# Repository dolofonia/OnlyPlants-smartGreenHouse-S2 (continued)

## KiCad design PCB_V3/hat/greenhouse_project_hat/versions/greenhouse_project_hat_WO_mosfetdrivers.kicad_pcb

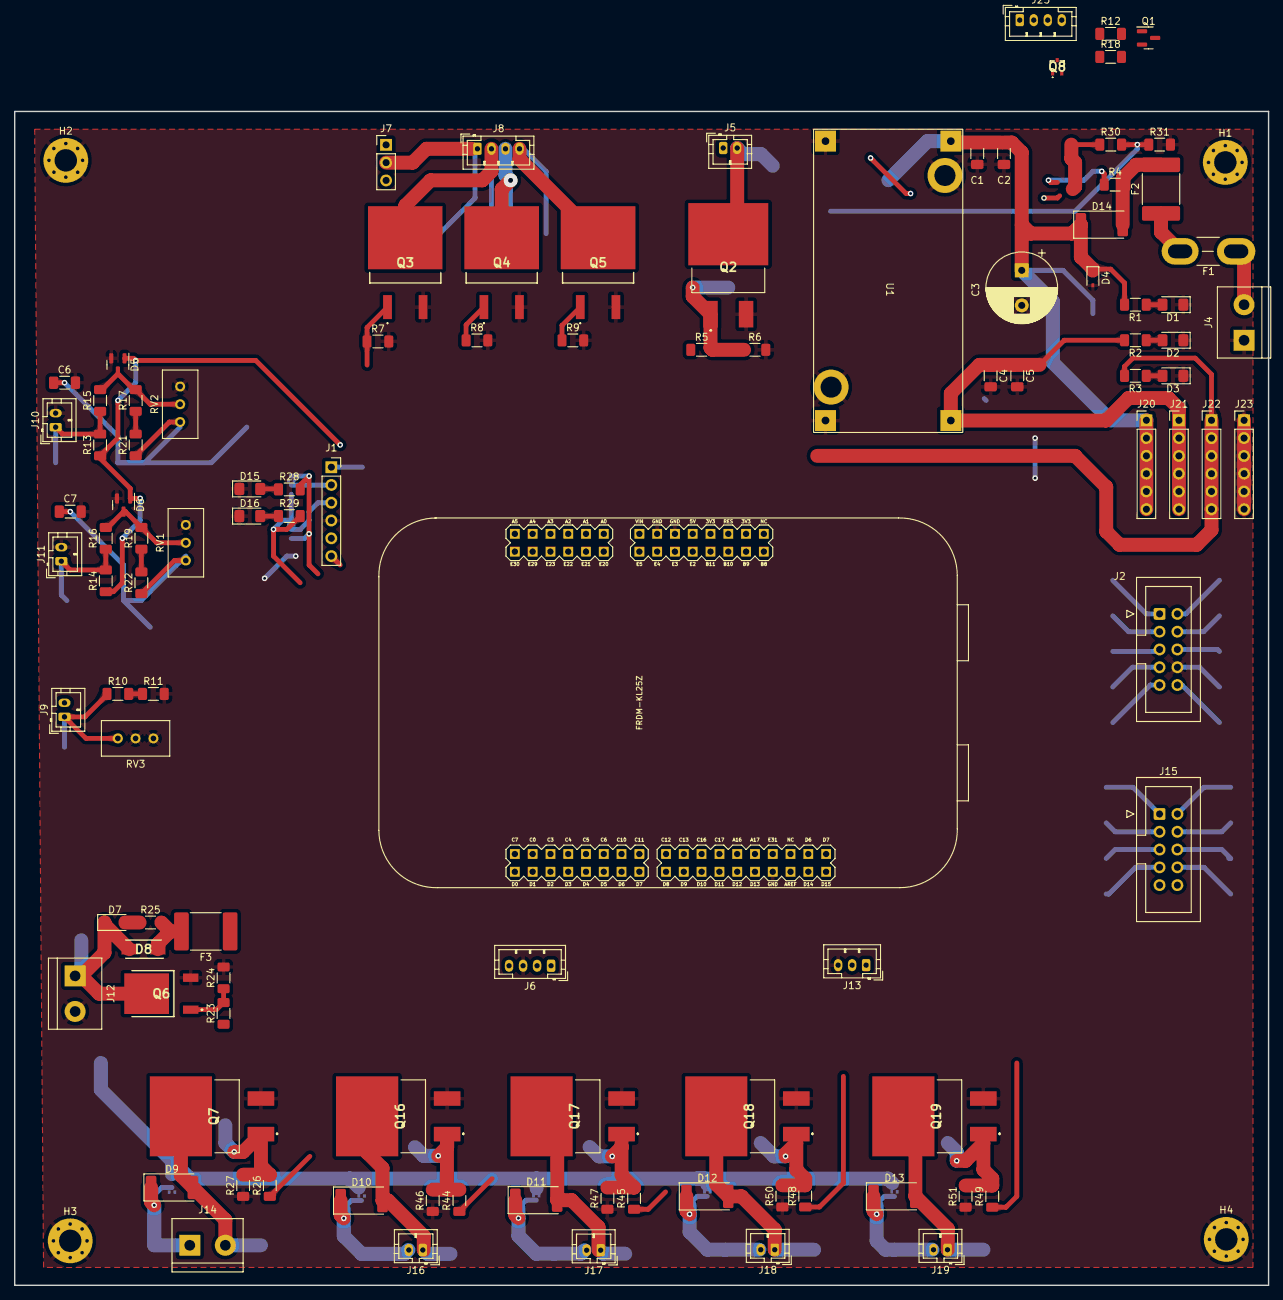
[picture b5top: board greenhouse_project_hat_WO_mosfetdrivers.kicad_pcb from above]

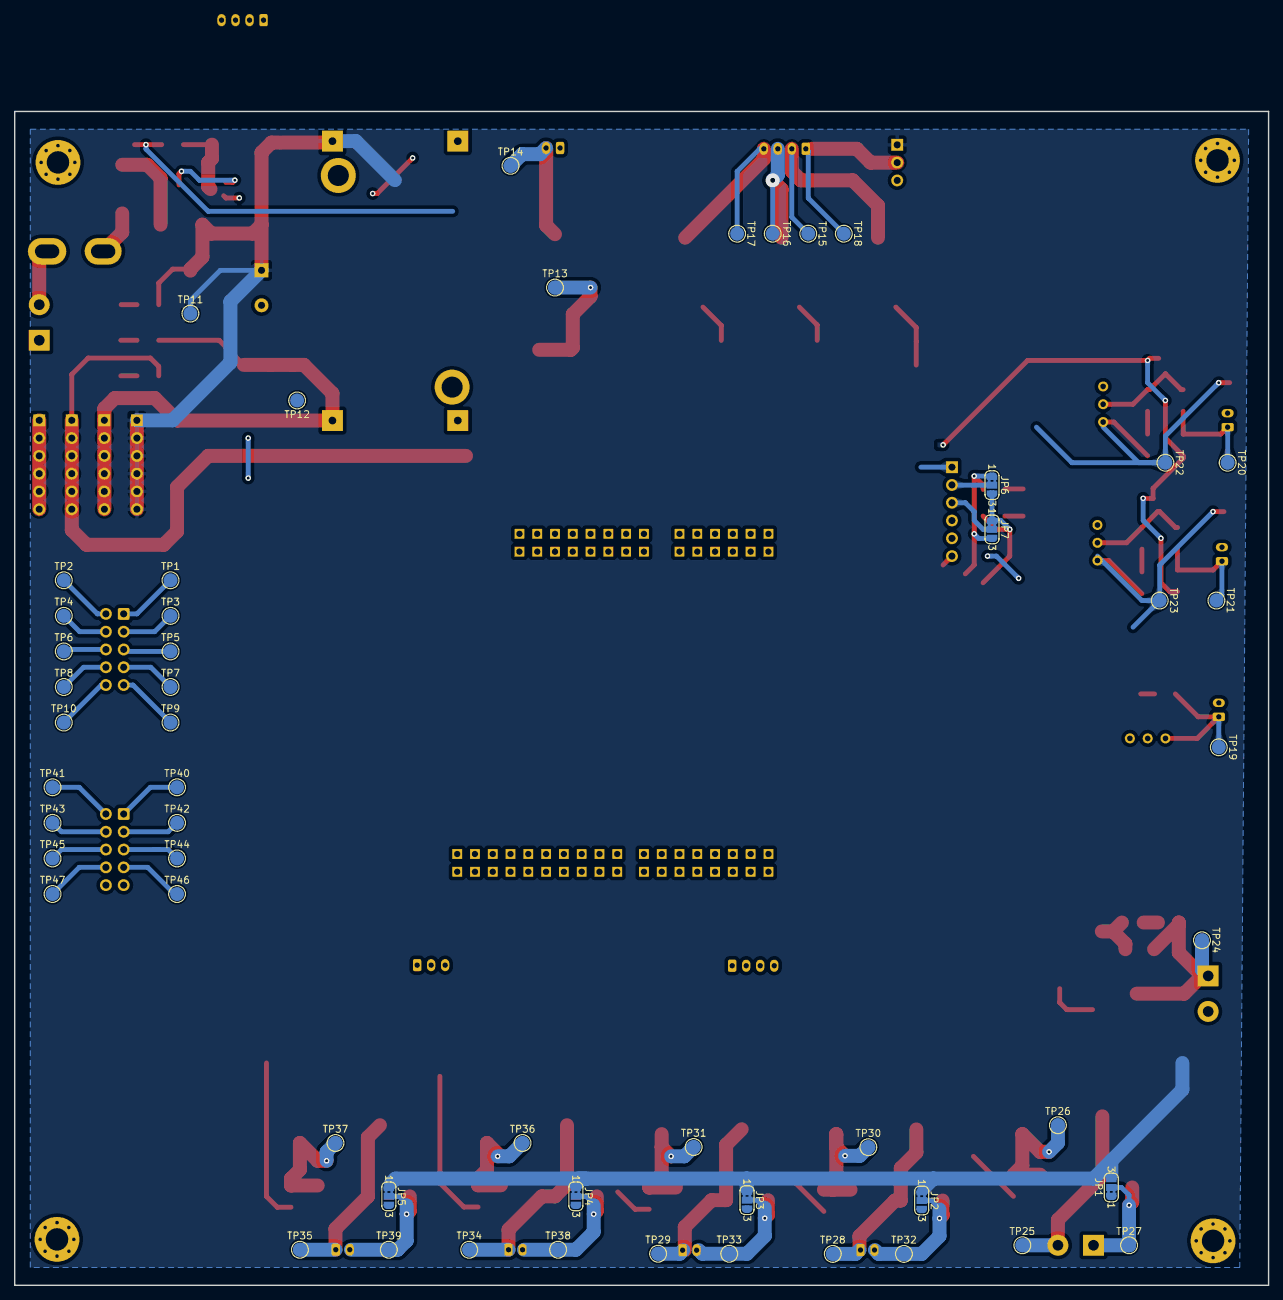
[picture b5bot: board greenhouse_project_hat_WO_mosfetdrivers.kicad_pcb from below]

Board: 4 copper layers, 179.1 x 167.6 mm, 166 parts (57 on the bottom side), 87 nets.

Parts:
C1, C5, C6, C7: 0.1uF; C_1206_3216Metric_Pad1.33x1.80mm_HandSolder
C2, C4: 10uF; C_1206_3216Metric_Pad1.33x1.80mm_HandSolder
C3: 1000uF; CP_Radial_D10.0mm_P5.00mm
D1, D2, D3, D7, D15, D16: LED; LED_1206_3216Metric_Pad1.42x1.75mm_HandSolder
D4: BZX384-A13-QX; D_SOD-323
D5, D6: BAV99; SOT-23
D8: SS54; DIOM5126X245N
D9, D10, D11, D12, D13, D14: 1N4007; D_2512_6332Metric_Pad1.52x3.35mm_HandSolder
F1: Fuse; Fuse_Blade_Mini_directSolder
F2, F3: Polyfuse; Fuse_2920_7451Metric_Pad2.10x5.45mm_HandSolder
FRDM1: FRDM-KL25Z; FRDM_KL25Z_NORMAL
G1: LOGO; logo
H1, H2, H3, H4: MountingHole_Pad; MountingHole_3.2mm_M3_Pad_Via
J1: Conn_01x06_Socket; PinSocket_1x06_P2.54mm_Vertical
J2, J15: Conn_01x10_Socket; IDC-Header_2x05_P2.54mm_Vertical
J4, J12, J14: Screw_Terminal_01x02; TerminalBlock_bornier-2_P5.08mm
J5, J9, J10, J11, J16, J17, J18, J19: Conn_01x02_Socket; JST_PH_B2B-PH-K_1x02_P2.00mm_Vertical
J6, J8, J25: Conn_01x04_Socket; JST_PH_B4B-PH-K_1x04_P2.00mm_Vertical
J7: Conn_01x03_Pin; PinHeader_1x03_P2.54mm_Vertical
J13: Conn_01x03_Socket; JST_PH_B3B-PH-K_1x03_P2.00mm_Vertical
J20, J21, J22, J23: Conn_01x06_Pin; PinHeader_1x06_P2.54mm_Vertical
JP1, JP2, JP3, JP4, JP5, JP6, JP7: Jumper_3_Bridged12; SolderJumper-3_P1.3mm_Bridged2Bar12_RoundedPad1.0x1.5mm_Num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
Q1: AO3401A; SOT-23
Q2, Q7, Q16, Q17, Q18, Q19: IRLZ44NSTRLPBF; IRF2804STRLPBF
Q3, Q4, Q5: IRF640S
Q6: IPD036N04LGATMA1
Q8: RZF030P01; 2SB1730
R1, R6, R7, R8, R9, R23, R27, R46, R47, R50, R51: 10k; R_1206_3216Metric_Pad1.30x1.75mm_HandSolder
R2, R13, R14, R25: 4.7k; R_1206_3216Metric_Pad1.30x1.75mm_HandSolder
R3, R5, R26, R44, R45, R48, R49: 2.2k; R_1206_3216Metric_Pad1.30x1.75mm_HandSolder
R4, R12, R18: 165; R_1206_3216Metric_Pad1.30x1.75mm_HandSolder
R10: 100k; R_1206_3216Metric_Pad1.30x1.75mm_HandSolder
R11, R21, R22: 0; R_1206_3216Metric_Pad1.30x1.75mm_HandSolder
R15, R16, R17, R19: 2.37k 1%; R_1206_3216Metric_Pad1.30x1.75mm_HandSolder
R24: 12k; R_1206_3216Metric_Pad1.30x1.75mm_HandSolder
R28, R29: 5k; R_1206_3216Metric_Pad1.30x1.75mm_HandSolder
R30: 49.9K; R_1206_3216Metric_Pad1.30x1.75mm_HandSolder
R31: 10K; R_1206_3216Metric_Pad1.30x1.75mm_HandSolder
REF1: KiCad-Logo2_5mm_SilkScreen
REF2: WEEE-Logo_4.2x6mm_SilkScreen
REF3: ESD-Logo_6.6x6mm_SilkScreen
RV1, RV2, RV3: R_Potentiometer; Potentiometer_Bourns_3296W_Vertical
TP1, TP2, TP3, TP4, TP5, TP6, TP7, TP8, TP9, TP10, TP11, TP12, TP13, TP14, TP15, TP16, TP17, TP18, TP19, TP20, TP21, TP22, TP23, TP24, TP25, TP26, TP27, TP28, TP29, TP30, TP31, TP32, TP33, TP34, TP35, TP36, TP37, TP38, TP39, TP40, TP41, TP42, TP43, TP44, TP45, TP46, TP47: TestPoint; TestPoint_Pad_D2.0mm
U1: LM2596 Buck; LM2596_Buck_module

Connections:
+3.3V: D5.1 (K), D6.1 (K), FRDM1.P3V3 (3V3), J2.7, J22.1, J22.2, J22.3, J22.4, J22.5, J22.6, R3.2, R12.1, R13.1, R14.1, TP7.1
+5V: C4.1, C5.1, FRDM1.VIN, J1.5, J2.6, J5.1, J6.1, J7.3, J9.2, J13.2, J15.9, J21.1, J21.2, J21.3, J21.4, J21.5, J21.6, J25.2, JP1.1 (A), JP2.3 (B), JP3.3 (B), JP4.3 (B), JP5.3 (B), Q8.2, R2.2, TP6.1, TP12.1, U1.3 (OUT+)
+12V: C1.1, C2.1, C3.1, D4.1 (K), D14.1 (K), F3.1, J7.1, J20.1, J20.2, J20.3, J20.4, J20.5, J20.6, JP1.3 (B), JP2.1 (A), JP3.1 (A), JP4.1 (A), JP5.1 (A), R1.2, TP11.1, U1.1 (IN+)
/BT_EN: FRDM1.PTE29, J1.6
/BT_RXD: FRDM1.PTE23, JP6.1 (A), JP7.3 (B), R28.2
/BT_RXD_O: J1.2, JP6.2 (C)
/BT_STATE: FRDM1.PTE21, J1.1
/BT_TXD: FRDM1.PTE22, JP6.3 (B), JP7.1 (A), R29.2
/BT_TXD_O: J1.3, JP7.2 (C)
/Fans/Fan1+: D10.1 (K), J16.2, JP2.2 (C), TP32.1
/Fans/Fan1-: D10.2 (A), J16.1, Q16.2, TP28.1
/Fans/Fan2+: D11.1 (K), J17.2, JP3.2 (C), TP33.1
/Fans/Fan2-: D11.2 (A), J17.1, Q17.2, TP29.1
/Fans/Fan3+: D12.1 (K), J18.2, JP4.2 (C), TP38.1
/Fans/Fan3-: D12.2 (A), J18.1, Q18.2, TP34.1
/Fans/Fan4+: D13.1 (K), J19.2, JP5.2 (C), TP39.1
/Fans/Fan4-: D13.2 (A), J19.1, Q19.2, TP35.1
/Heating/BED_OUT: D7.1 (K), D8.2, J12.1, Q6.2, TP24.1
/Humidifier/MIST-: J5.2, Q2.2, TP14.1
/OLED_SCL: FRDM1.D15 (SCL/PTE1), J2.10, TP10.1
/OLED_SDA: FRDM1.D14 (SDA/PTE0), J2.9, TP9.1
/Power/BATT_EN: D14.2 (A), F2.2, R4.2, R18.2
/Power/BATT_IN: J25.4, Q8.3, R30.1
/SW1_OUT: FRDM1.PTE2, J2.1, TP1.1
/SW2_OUT: FRDM1.PTE3, J2.2, TP2.1
/SW3_OUT: FRDM1.PTE4, J2.3, TP3.1
/SW4_OUT: FRDM1.PTE5, J2.4, TP4.1
/SW5_OUT: FRDM1.D6 (D6/PTC8), J2.5, TP5.1
/Water/Pump+: D9.1 (K), J14.1, JP1.2 (C), TP27.1
/Water/Pump-: D9.2 (A), J14.2, Q7.2, TP25.1
AHT_SCL: FRDM1.PTC10, J6.4
AHT_SDA: FRDM1.PTC11, J6.2
BATT_V: FRDM1.PTE30, R30.2, R31.1
B_IN: FRDM1.D7 (D7/PTC9), Q5.1, R9.1
FAN1_IN: FRDM1.D10 (D10/PTD0), R44.1
FAN2_IN: FRDM1.D11 (D11/PTD2), R45.1
FAN3_IN: FRDM1.D12 (D12/PTD3), R48.1
FAN4_IN: FRDM1.D13 (D13/PTD1), R49.1
GNDREF: C1.2, C2.2, C3.2, C4.2, C5.2, C6.2, C7.2, D1.1 (K), D2.1 (K), D3.1 (K), D4.2 (A), D5.2 (A), D6.2 (A), D15.1 (K), D16.1 (K), FRDM1.GND0, FRDM1.GND1, FRDM1.GND2, H1.1, H2.1, H3.1, H4.1, J1.4, J2.8, J4.1, J6.3, J10.2, J11.2, J12.2, J13.3, J23.1, J23.2, J23.3, J23.4, J23.5, J23.6, J25.1, J25.3, Q2.3, Q3.3, Q4.3, Q5.3, Q6.3, Q7.3, Q16.3, Q17.3, Q18.3, Q19.3, R6.2, R7.2, R8.2, R9.2, R11.2, R24.2, R27.1, R31.2, R46.1, R47.1, R50.1, R51.1, RV1.1, RV2.1, RV3.2, RV3.3, TP8.1, U1.2 (IN-), U1.4 (OUT-), U1.5 (GND1), U1.6 (GND2)
G_IN: FRDM1.PTE20, Q4.1, R8.1
HEATER_IN: FRDM1.A2 (A2/PTB2), R23.1
HUM_OUT: FRDM1.PTD6, J13.1
LDR_OUT: FRDM1.D9 (D9/PTD5), J9.1, R10.1, RV3.1, TP19.1
MIST_EN: FRDM1.PTC6, R5.1
unnamed: D1.2 (A), R1.1
unnamed: D2.2 (A), R2.1
unnamed: D3.2 (A), R3.1
unnamed: D5.3 (K), R15.2, R17.2, RV2.2
unnamed: D6.3 (K), R16.2, R19.2, RV1.2
unnamed: D7.2 (A), R25.1
unnamed: D8.1, F3.2, R25.2
unnamed: D15.2 (A), R28.1
unnamed: D16.2 (A), R29.1
unnamed: F1.2, F2.1
unnamed: J7.2, J8.1, TP18.1
unnamed: J8.2, Q3.2, TP15.1
unnamed: J8.3, Q4.2, TP16.1
unnamed: J8.4, Q5.2, TP17.1
unnamed: J10.1, R13.2, R15.1, TP20.1
unnamed: J11.1, R14.2, R16.1, TP21.1
unnamed: Q1.3 (D), R12.2
unnamed: Q1.1 (G), R18.1
unnamed: Q2.1, R5.2, R6.1, TP13.1
unnamed: Q6.1, R23.2, R24.1
unnamed: Q7.1, R26.2, R27.2, TP26.1
unnamed: Q8.1, R4.1
unnamed: Q16.1, R44.2, R46.2, TP30.1
unnamed: Q17.1, R45.2, R47.2, TP31.1
unnamed: Q18.1, R48.2, R50.2, TP36.1
unnamed: Q19.1, R49.2, R51.2, TP37.1
unnamed: R10.2, R11.1
unnamed: R17.1, R21.2
unnamed: R19.1, R22.2
PUMP_IN: FRDM1.D8 (D8/PTA13), R26.1
R_IN: FRDM1.PTE31, Q3.1, R7.1
SENS1: FRDM1.PTC12, J15.1, TP40.1
SENS2: FRDM1.PTC13, J15.2, TP41.1
SENS3: FRDM1.PTC16, J15.3, TP42.1
SENS4: FRDM1.PTC17, J15.4, TP43.1
SENS5: FRDM1.PTA16, J15.5, TP44.1
SENS6: FRDM1.PTA17, J15.6, TP45.1
SENS7: FRDM1.D5 (D5/PTA5), J15.7, TP46.1
SENS8: FRDM1.PTD7, J15.8, TP47.1
THERM1: C6.1, FRDM1.A0 (A0/PTB0), R21.1, RV2.3, TP22.1
THERM2: C7.1, FRDM1.A1 (A1/PTB1), R22.1, RV1.3, TP23.1
VDC: F1.1, J4.2
~12V_EN: FRDM1.PTB8, Q1.2 (S)

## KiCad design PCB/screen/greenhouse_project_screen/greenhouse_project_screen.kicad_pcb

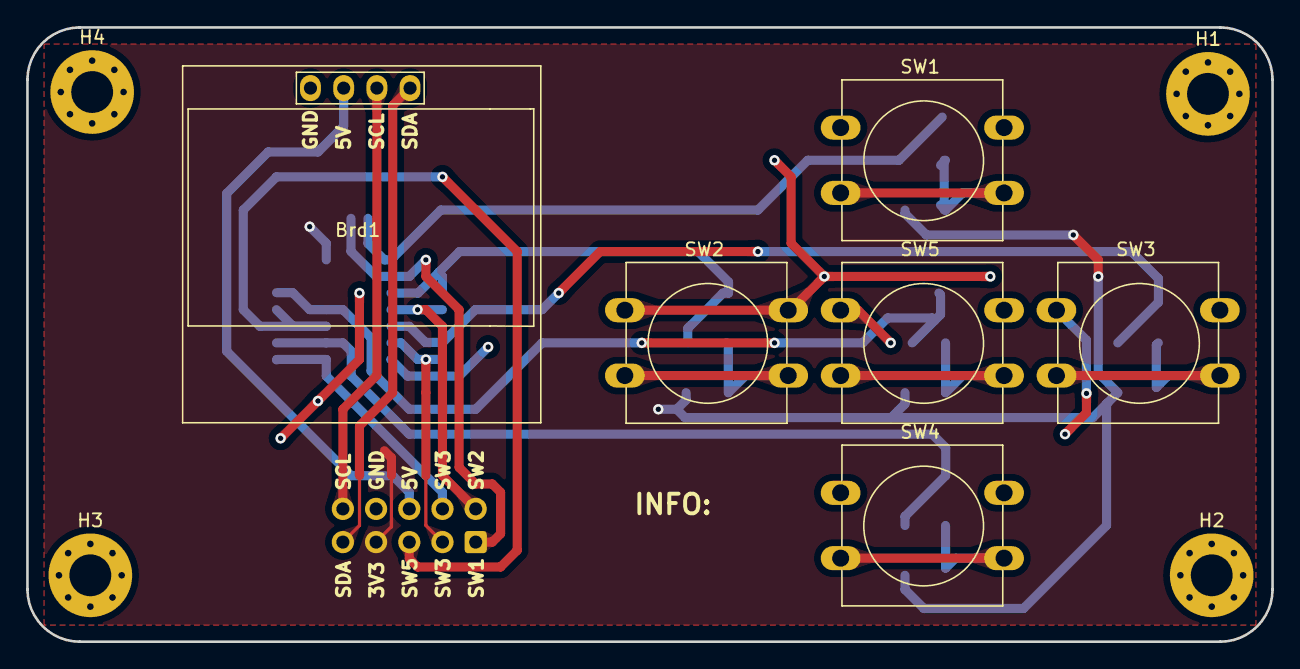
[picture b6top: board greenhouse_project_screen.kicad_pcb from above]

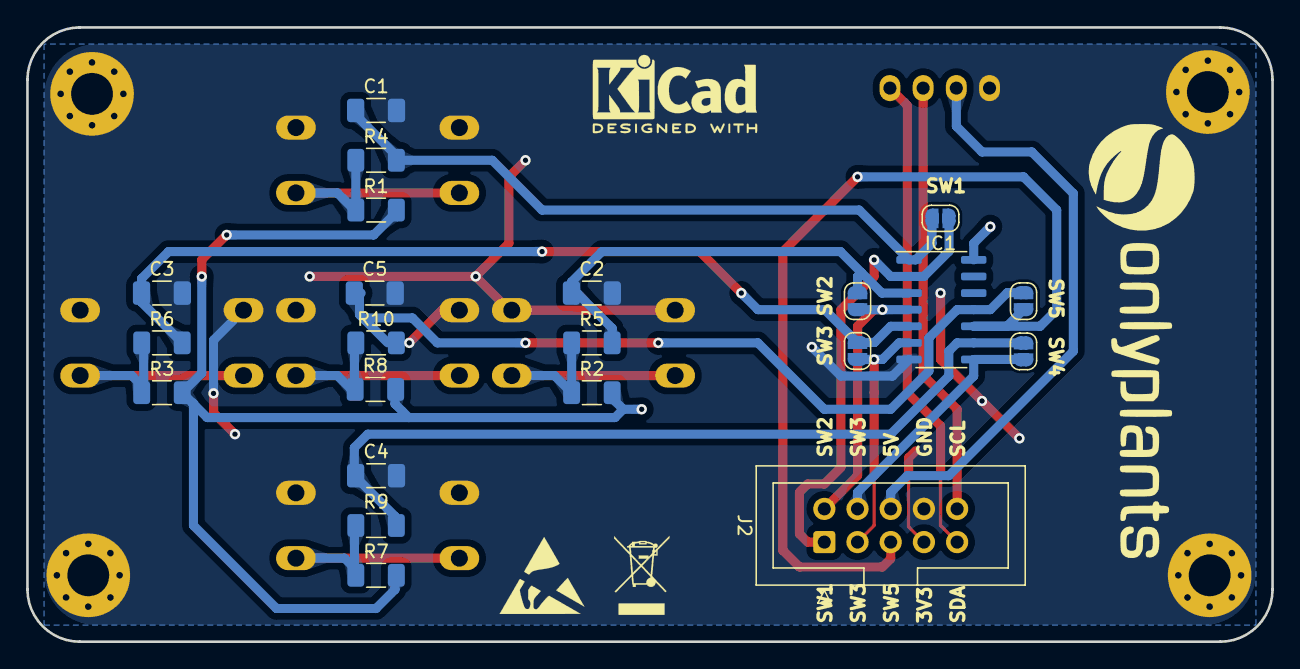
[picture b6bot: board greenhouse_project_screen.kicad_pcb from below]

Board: 2 copper layers, 95.2 x 47.0 mm, 32 parts (22 on the bottom side), 20 nets.

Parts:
Brd1: SSD1306; 128x64OLED
C1, C2, C3, C4, C5: 10uF; C_1206_3216Metric_Pad1.33x1.80mm_HandSolder
H1, H2, H3, H4: MountingHole_Pad; MountingHole_3.2mm_M3_Pad_Via
IC1: CD74HC14M96; SOIC-14_3.9x8.7mm_P1.27mm
J2: Conn_01x10_Socket; IDC-Header_2x05_P2.54mm_Vertical
JP1, JP2, JP3, JP4, JP5: Jumper_2_Open; SolderJumper-2_P1.3mm_Open_RoundedPad1.0x1.5mm
R1, R4: 10k; R_1206_3216Metric_Pad1.30x1.75mm_HandSolder
R2, R3, R5, R6, R7, R8, R9, R10: 10K; R_1206_3216Metric_Pad1.30x1.75mm_HandSolder
SW1, SW2, SW3, SW4, SW5: SW_Push; SW_PUSH-12mm

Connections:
+3.3V: IC1.14 (VCC), J2.7, R1.2, R2.2, R3.2, R7.2, R8.2
+5V: Brd1.2 (VCC), J2.6
/IN_SW1: C1.1, IC1.1 (1A), JP1.1 (A), R4.2
/IN_SW2: C2.1, IC1.3 (2A), JP2.2 (B), R5.2
/IN_SW3: C3.1, IC1.5 (3A), JP3.2 (B), R6.2
/IN_SW4: C4.1, IC1.9 (4A), JP4.1 (A), R9.2
/IN_SW5: C5.1, IC1.11 (5A), JP5.1 (A), R10.2
/OUT_SW1: IC1.2 (1Y), J2.1, JP1.2 (B)
/OUT_SW2: IC1.4 (2Y), J2.2, JP2.1 (A)
/OUT_SW3: IC1.6 (3Y), J2.3, JP3.1 (A)
/OUT_SW4: IC1.8 (4Y), J2.4, JP4.2 (B)
/OUT_SW5: IC1.10 (5Y), J2.5, JP5.2 (B)
/SCL: Brd1.3 (SCL), J2.10
/SDA: Brd1.4 (SDA), J2.9
GNDREF: Brd1.1 (GND), C1.2, C2.2, C3.2, C4.2, C5.2, H1.1, H2.1, H3.1, H4.1, IC1.7 (GND), J2.8, SW1.1, SW2.1, SW3.1, SW4.1, SW5.1
unnamed: R1.1, R4.1, SW1.2
unnamed: R2.1, R5.1, SW2.2
unnamed: R3.1, R6.1, SW3.2
unnamed: R7.1, R9.1, SW4.2
unnamed: R8.1, R10.1, SW5.2

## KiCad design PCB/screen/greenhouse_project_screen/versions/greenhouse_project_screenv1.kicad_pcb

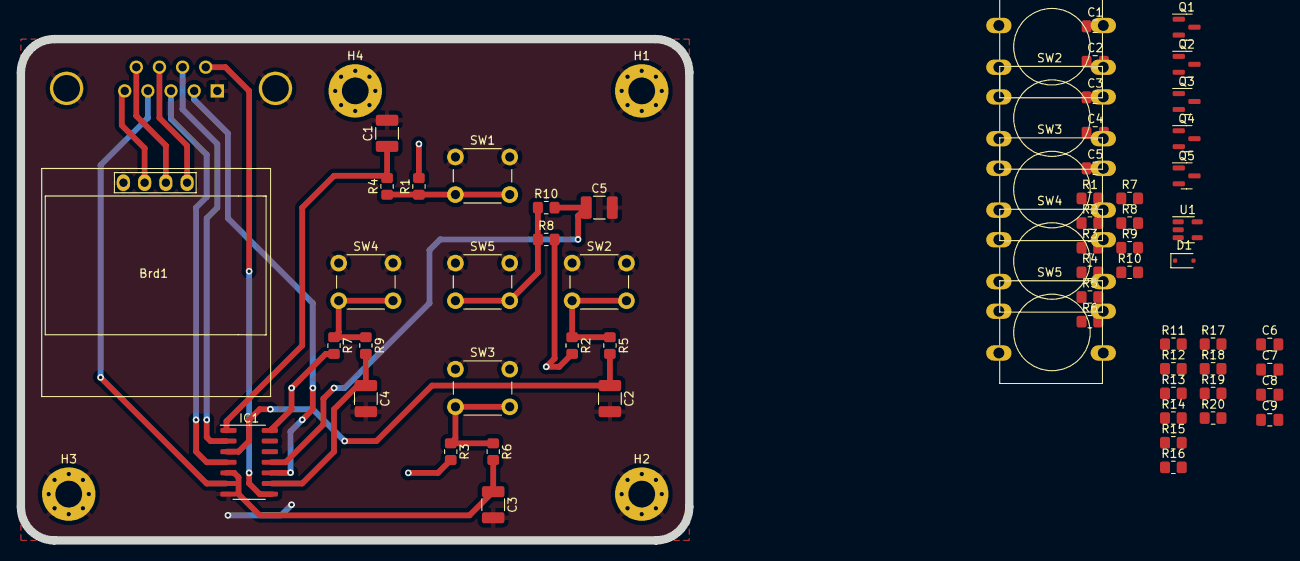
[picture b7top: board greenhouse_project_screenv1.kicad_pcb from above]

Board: 2 copper layers, 80.0 x 60.0 mm, 68 parts (1 on the bottom side), 37 nets.

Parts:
Brd1: SSD1306; 128x64OLED
C1, C2#2, C3#2, C4, C5: C; C_1210_3225Metric_Pad1.33x2.70mm_HandSolder
C1#2, C2, C3, C4#2, C5#2: C; C_0805_2012Metric_Pad1.18x1.45mm_HandSolder
C6, C7, C8, C9: 1uF 16v; C_0805_2012Metric_Pad1.18x1.45mm_HandSolder
D1: PMEG3010EJ; D_SOD-323F
H1, H2, H3, H4: MountingHole_Pad; MountingHole_3.2mm_M3_Pad_Via
IC1: CD74HC14M96; SOIC-14_3.9x8.7mm_P1.27mm
J1: DB9_Female_MountingHoles; DSUB-9_Female_Horizontal_P2.77x2.84mm_EdgePinOffset4.94mm_H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
Q1, Q2, Q3, Q4, Q5: BSS138; SOT-23
R1, R1#2, R2, R2#2, R3, R3#2, R4, R4#2, R5, R5#2, R6, R6#2, R7, R7#2, R8, R8#2, R9, R9#2, R10, R10#2: R; R_0805_2012Metric_Pad1.20x1.40mm_HandSolder
R11, R12, R13, R14, R15, R16, R17, R18, R19, R20: 10k; R_0805_2012Metric_Pad1.20x1.40mm_HandSolder
SW1, SW2#2, SW3, SW4, SW5: SW_Push; SW_PUSH-12mm
SW1#2, SW2, SW3#2, SW4#2, SW5#2: SW_Push; SW_PUSH_6mm_H13mm
U1: TLV75533PDBV; SOT-23-5

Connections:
+3.3V: C8.1, C9.1, IC1.14 (VCC), Q1.1 (G), Q2.1 (G), Q3.1 (G), Q4.1 (G), Q5.1 (G), R11.1, R13.1, R15.1, R17.1, R19.1, U1.5 (OUT)
+5V: Brd1.2 (VCC), D1.2 (A), J1.5, R1.2, R1#2.2, R2.2, R2#2.2, R3.2, R3#2.2, R7.2, R7#2.2, R8.2, R8#2.2, R12.1, R14.1, R16.1, R18.1, R20.1
/Buttons/IN_SW1: C1#2.1, R4.2
/Buttons/IN_SW2: C2.1, R5.2
/Buttons/IN_SW3: C3.1, R6#2.2
/Buttons/IN_SW4: C4#2.1, R9#2.2
/Buttons/IN_SW5: C5#2.1, R10#2.2
/IN_SW1: C1.1, R4#2.2
/IN_SW2: C2#2.1, R5#2.2
/IN_SW3: C3#2.1, R6.2
/IN_SW4: C4.1, IC1.9 (4A), R9.2
/IN_SW5: C5.1, R10.2
/Level shifting/LVL_SW1: Q1.3 (D), R12.2
/Level shifting/LVL_SW2: Q2.3 (D), R14.2
/Level shifting/LVL_SW3: Q3.3 (D), R16.2
/Level shifting/LVL_SW4: Q4.3 (D), R18.2
/Level shifting/LVL_SW5: Q5.3 (D), R20.2
/Level shifting/OUT_SW1: Q1.2 (S), R11.2
/Level shifting/OUT_SW2: Q2.2 (S), R13.2
/Level shifting/OUT_SW3: Q3.2 (S), R15.2
/Level shifting/OUT_SW4: Q4.2 (S), R17.2
/Level shifting/OUT_SW5: Q5.2 (S), R19.2
/OUT_SW1: IC1.2 (1Y), J1.7
/OUT_SW2: IC1.4 (2Y), J1.3
/OUT_SW3: IC1.6 (3Y), J1.4
/OUT_SW4: IC1.8 (4Y), J1.6
/OUT_SW5: IC1.10 (5Y), J1.2
/SCL: Brd1.3 (SCL), J1.9
/SDA: Brd1.4 (SDA), J1.8
GND: C6.2, C7.2, C8.2, C9.2, U1.2 (GND)
GNDREF: Brd1.1 (GND), C1.2, C1#2.2, C2.2, C2#2.2, C3.2, C3#2.2, C4.2, C4#2.2, C5.2, C5#2.2, H1.1, H2.1, H3.1, H4.1, IC1.7 (GND), J1.0 (PAD), J1.1, SW1.1, SW1#2.1, SW2.1, SW2#2.1, SW3.1, SW3#2.1, SW4.1, SW4#2.1, SW5.1, SW5#2.1
unnamed: C6.1, C7.1, D1.1 (K), U1.1 (IN), U1.3 (EN)
unnamed: R1.1, R1#2.1, R4.1, R4#2.1, SW1.2, SW1#2.2
unnamed: R2.1, R2#2.1, R5.1, R5#2.1, SW2.2, SW2#2.2
unnamed: R3.1, R3#2.1, R6.1, R6#2.1, SW3.2, SW3#2.2
unnamed: R7.1, R7#2.1, R9.1, R9#2.1, SW4.2, SW4#2.2
unnamed: R8.1, R8#2.1, R10.1, R10#2.1, SW5.2, SW5#2.2

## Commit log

2023-02-02 test
2023-02-02 Delete test.docx
    test
2023-03-18 Updated PCB files
2023-03-18 Update: hat V5.0
2023-03-18 dfvb
2023-04-12 First production version
2023-06-20 Uploaded finals
    Pushed the final versions of the microcontroller code, Nodered code, PCB and CAD files to the repository
